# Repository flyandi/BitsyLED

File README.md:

<h1 align="center">
	
	<br />
	BitsyLED 
</h1>
<p align="center">
	A minimal firmware and configurator to drive RGB LED's
</p>

---

Click below for a video:

# Introduction

BitsyLED is a minimal firmware to drive RGB LED's (WS2811, WS2812, NeoPixels, etc). It's designed for anything RC but also can be used for other projects including Christmas lights, Lego's, or even your real car.

BitsyLED is divided into two parts: The Firmware and the Configurator. The firmware can be run on most Arduino compatible boards and I also created a dedicated board (see below) that is targeted primarily for RC purposes.

## Features

By default the firmware is set to the following settings which is the maximum amount supported by the ATTINY. The firmware can be reconfigured through the file `config.h`.

* Up to 5 individual ranges, selectable through either an RC PWM signal, Analog signal, Time based or always on.

* 3 LED data strands per range (Left, Right, Other)

* Each data strand can have up to 10 LED's

* Supports multiple patterns such as Off, Solid, Blink, Strobe and Pulse. 

* Supports different speeds per pattern

* Simulate your patterns directly through the BitsyLED configurator

## Status

The configurator and firmware are still under development but some parts may change as I have time to complete the following objectives:

- Introduce curves for custom light patterns (Pending)
- Add presets (Pending)
- Add serial debug output (In Progress)
- More documentation (getting there)
- Upload firmware directly from the configurator (Pending)

## Firmware

The firmware is designed for Arduino compatible boards. I also created a dedicated board called the BitsyLED board.

The default firmware configuration is setup for the BitsyLED board which sports a 8bit ATTINY84 that supports up to 5 selectable configurations. Each configuration can have 3 data strands with up to 10 LED's per strand. 

The firmware can be reconfigured as needed via the `config.h` file. 

### Board Support

| Board | Ranges | Strands/Range | LED's/Strand | Possible Combinations | Config |
| ----  | ------ | ------------- | ------------ | --------------------- | ------- | 
| BitsyLED | 5 | 3 | 10 | 150 | `BOARD_BITSYLED` in `config.h` |
| Arduino | 6 | 3 | 25 | 450 | `BOARD_ARDUINO` in `config.h` |

## Configurator

The configurator is a visual tool that allows easy setup of LED's and supports various effects such blinking, strobe and pulsing.

It allows to setup different selectable ranges which can be controlled via an PWM RC signal, a 10k Analog Potentiometer or based on Time (TBD).

### Installation

The configurator is available as standalone app since Google has dropped support for Chrome Apps. Please download the latest release for your platform from the `releases` tab.

Once installed, the application will automatically updates itself once new versions are released.

## Hardware

Right now I don't offer a complete build of the BitsyLED board however you can order your own copy on Oshpark. 

Alternatively the firmware runs perfectly fine on any Arduino compatible board with the caveat that the firmware and configurator settings are statically aligned to the Arduino Pro Mini with a maximum of 1024bytes of EEPROM.

### v1.2.1 (Latest)

https://oshpark.com/shared_projects/B3IAiNyH

I created a new board that is slimmer and has SMD pad's instead of the drill pad's which gives it more flexibility. The board also comes with an status LED.

#### Parts

All parts available on DigiKey.com. I changed some components in this version!

- 1x ATTINY84 (Part ATTINY84A-SSURCT-ND) 
- 1x Capacitor in 805 packaging (587-1304-1-ND) 
- 1x Diode in SOD-123 packaging (MMSZ5231B-TP)
- 1x Blue LED in 805 packaging (150080BS75000)
- 1x Resistor in 805 packaging with value of 140ohms (Part RMCF0805FT140R)

#### How to use the board

The board is divided into a top and bottom part. The top part includes the three data channel (Left, Right, Other) as well the input (RC, Analog). The header is designed to be foremost compatible with RC PWM signals (Signal + 5V + GND). 

Be careful not to mix up the upper and lower header from the front side as they are aligned with each other.

The board has 3 LED channels: Left, Right and Other; plus an input channel that either can be served by an RC-PWM or Analog signal. Ensure that your configuration includes the proper input.

The bottom board includes the same 6 position header however it's being used for two purposes: Firmware updates and Configuration.

Follow the connection diagram above how to connect your LED's and Input's.

You will need an USBASP to upload the Firmware and an serial capable board (like FTDI adapter) to upload the configuration from the configurator.

### v1.1 (For reference only)

https://oshpark.com/shared_projects/E85sUqFS

#### Parts

All parts available on DigiKey.com:

- 1x ATTINY84 (Part ATTINY84A-SSURCT-ND) 
- 1x Capacitor in 805 packaging (587-1304-1-ND) 
- 1x Diode in SOD-123 packaging (MMSZ5242B-TPMSCT-ND)

#### How to use the board

The board has 3 LED channels: Left, Right and Other; plus an input channel that either can be served by an RC-PWM or Analog signal. Ensure that your configuration selectest the proper input.

Additionally the board has a top and bottom SMD connector that is used as a dual function to upload the firmware and as serial port.

Follow the connection diagram below how to connect 

You will need an USBASP to upload the Firmware and an serial capable board (like FTDI adapter) to upload the configuration from the configurator.

### Future

Working on a new board with USB support.

### Arduino

As described above, the Arduino configuraton is statically aligned for the Arduino Pro Mini series which has by default an EEPROM size of `1024 bytes`.

However that amount of storage still results in up to `6` selectable ranges, each with `3` strands and up to `25` led's per strand.

The following pin map is being used for BitsyLED:

| Pin | Purpose | 
| ----  | ------ |
| 9 | Input for RC PWM or Analog |
| 10 | Left Strand Data Channel |
| 11 | Right Strand Data Channel |
| 12 | Other Strand Data Channel |

Also if enabled, BitsyLED will use the internal LED on pin `13` as status LED.

## Installation

Please download the latest binary from the releases tab or clone this project and build your own version. 

For firmware, you will need the Arduino IDE (easiest). Clone this project and ipen the `bitsyled.ino` in the `firmware` folder. Follow the direction for your board to upload.

For the BitsyLED board you need to install ATTINY board support into your IDE.

## Links

For support, help or discussion please visit my official thread on RCGroups: 

https://www.rcgroups.com/forums/showthread.php?3289805-BitsyLED

For regular project updates please visit the project on hackaday.io:

https://hackaday.io/project/165227-bitsyled

## License

This program is free software: you can redistribute it and/or modify
it under the terms of the GNU General Public License as published by
the Free Software Foundation, either version 3 of the License, or
(at your option) any later version.

This program is distributed in the hope that it will be useful,
but WITHOUT ANY WARRANTY; without even the implied warranty of
MERCHANTABILITY or FITNESS FOR A PARTICULAR PURPOSE. See the
GNU General Public License for more details.

You should have received a copy of the GNU General Public License
along with this program. If not, see <http://www.gnu.org/licenses/>

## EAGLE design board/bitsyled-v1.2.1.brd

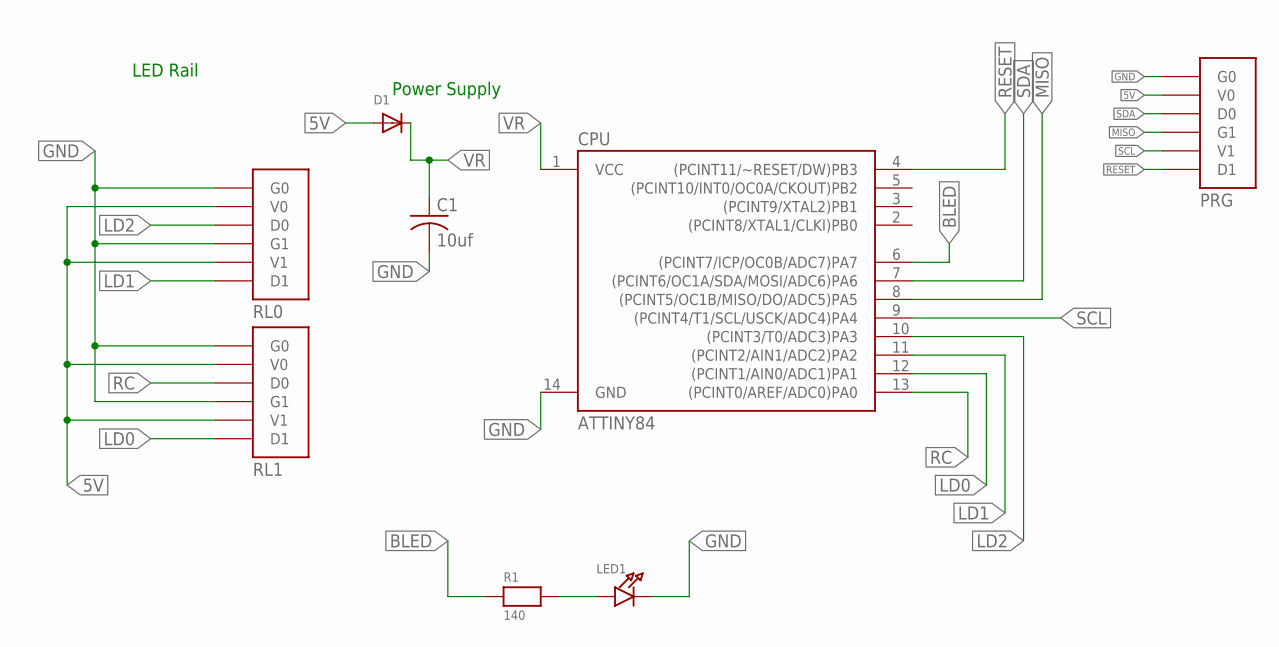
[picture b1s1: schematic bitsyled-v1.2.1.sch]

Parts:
C1: 10uf; C0805
CPU: ATTINY84; SO14
D1: DIODESOD-123; SOD-123
LED1: LED0805_NOOUTLINE; CHIPLED_0805_NOOUTLINE
PRG: BITSYLED_1X6_RAILPRG; BITSYLED_1X6_RAIL_PRG
R1: 140; _0805
RL0: BITSYLED_1X6_RAILNORMAL; BITSYLED_1X6_RAIL
RL1: BITSYLED_1X6_RAILREVERSED; BITSYLED_1X6_RAIL_R

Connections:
5V: D1.A, PRG.V0, RL0.V0, RL0.V1, RL1.V0, RL1.V1
BLED: CPU.6 ((PCINT7/ICP/OC0B/ADC7)PA7), R1.1
GND: C1.2, CPU.14 (GND), LED1.C, PRG.G0, RL0.G0, RL0.G1, RL1.G0, RL1.G1
LD0: CPU.12 ((PCINT1/AIN0/ADC1)PA1), RL1.D1
LD1: CPU.11 ((PCINT2/AIN1/ADC2)PA2), RL0.D1
LD2: CPU.10 ((PCINT3/T0/ADC3)PA3), RL0.D0
MISO: CPU.8 ((PCINT5/OC1B/MISO/DO/ADC5)PA5), PRG.G1
unnamed: LED1.A, R1.2
RC: CPU.13 ((PCINT0/AREF/ADC0)PA0), RL1.D0
RESET: CPU.4 ((PCINT11/~RESET/DW)PB3), PRG.D1
SCL: CPU.9 ((PCINT4/T1/SCL/USCK/ADC4)PA4), PRG.V1
SDA: CPU.7 ((PCINT6/OC1A/SDA/MOSI/ADC6)PA6), PRG.D0
VR: C1.1, CPU.1 (VCC), D1.C

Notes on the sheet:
Power Supply
LED Rail

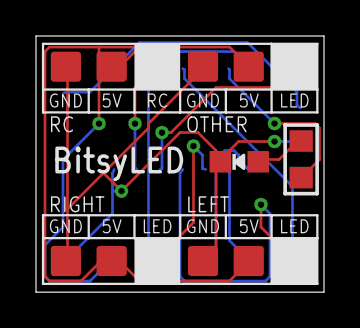
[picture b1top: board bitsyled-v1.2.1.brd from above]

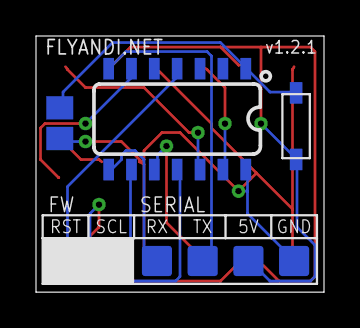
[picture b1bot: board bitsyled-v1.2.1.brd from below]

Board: 2 copper layers, 16.0 x 14.2 mm, 8 parts (3 on the bottom side), 13 nets.

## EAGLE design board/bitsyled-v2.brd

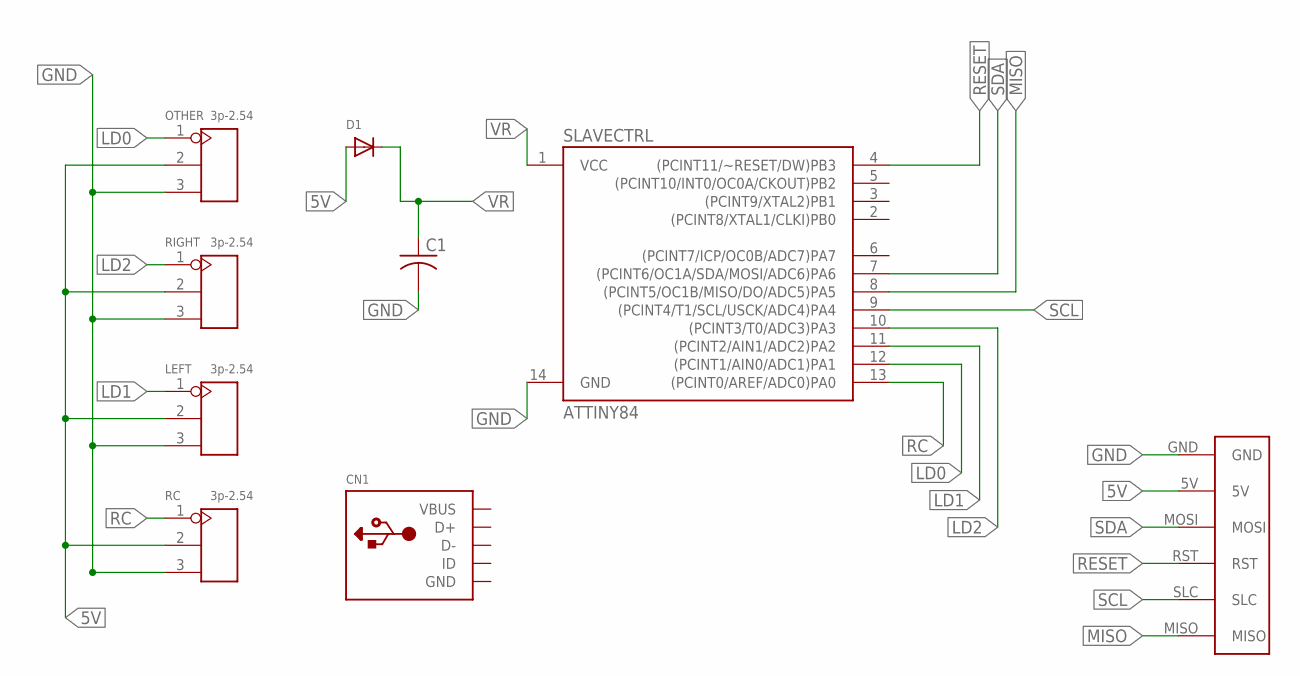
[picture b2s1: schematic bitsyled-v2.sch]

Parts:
C1: C-USC0805; C0805
CN1: USBMOLEX; USB-MINIB-THM-MOLEX
D1: DIODESOD-123; SOD-123
LEFT: 3p-2.54; H3-2.54
OTHER: 3p-2.54; H3-2.54
RC: 3p-2.54; H3-2.54
RIGHT: 3p-2.54; H3-2.54
SLAVECTRL: ATTINY84; SO14
U$1: SMDPAD_PRG

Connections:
5V: D1.A, LEFT.2, OTHER.2, RC.2, RIGHT.2, U$1.5V
GND: C1.2, CN1.GND, LEFT.3, OTHER.3, RC.3, RIGHT.3, SLAVECTRL.14 (GND), U$1.GND
LD0: OTHER.1, SLAVECTRL.12 ((PCINT1/AIN0/ADC1)PA1)
LD1: LEFT.1, SLAVECTRL.11 ((PCINT2/AIN1/ADC2)PA2)
LD2: RIGHT.1, SLAVECTRL.10 ((PCINT3/T0/ADC3)PA3)
MISO: SLAVECTRL.8 ((PCINT5/OC1B/MISO/DO/ADC5)PA5), U$1.MISO
RC: RC.1, SLAVECTRL.13 ((PCINT0/AREF/ADC0)PA0)
RESET: SLAVECTRL.4 ((PCINT11/~RESET/DW)PB3), U$1.RST
SCL: SLAVECTRL.9 ((PCINT4/T1/SCL/USCK/ADC4)PA4), U$1.SLC
SDA: SLAVECTRL.7 ((PCINT6/OC1A/SDA/MOSI/ADC6)PA6), U$1.MOSI
VBUS: CN1.VBUS
VR: C1.1, D1.C, SLAVECTRL.1 (VCC)

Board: 2 copper layers, 9 parts (1 on the bottom side), 11 nets, no tracks yet.

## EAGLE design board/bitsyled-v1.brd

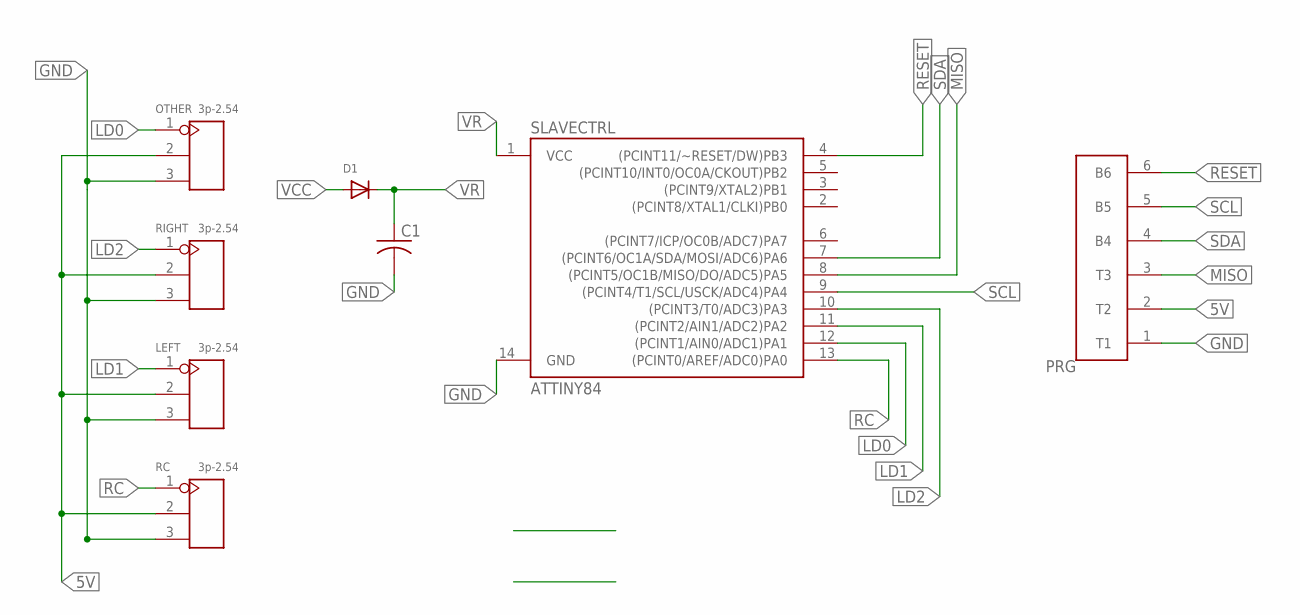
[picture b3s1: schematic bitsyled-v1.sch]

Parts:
C1: C-USC0805; C0805
D1: DIODESOD-123; SOD-123
LEFT: 3p-2.54; H3-2.54
OTHER: 3p-2.54; H3-2.54
PRG: SMDPAD_TB_3X3
RC: 3p-2.54; H3-2.54
RIGHT: 3p-2.54; H3-2.54
SLAVECTRL: ATTINY84; SO14

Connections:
5V: LEFT.2, OTHER.2, PRG.2 (T2), RC.2, RIGHT.2
GND: C1.2, LEFT.3, OTHER.3, PRG.1 (T1), RC.3, RIGHT.3, SLAVECTRL.14 (GND)
LD0: OTHER.1, SLAVECTRL.12 ((PCINT1/AIN0/ADC1)PA1)
LD1: LEFT.1, SLAVECTRL.11 ((PCINT2/AIN1/ADC2)PA2)
LD2: RIGHT.1, SLAVECTRL.10 ((PCINT3/T0/ADC3)PA3)
MISO: PRG.3 (T3), SLAVECTRL.8 ((PCINT5/OC1B/MISO/DO/ADC5)PA5)
RC: RC.1, SLAVECTRL.13 ((PCINT0/AREF/ADC0)PA0)
RESET: PRG.6 (B6), SLAVECTRL.4 ((PCINT11/~RESET/DW)PB3)
SCL: PRG.5 (B5), SLAVECTRL.9 ((PCINT4/T1/SCL/USCK/ADC4)PA4)
SDA: PRG.4 (B4), SLAVECTRL.7 ((PCINT6/OC1A/SDA/MOSI/ADC6)PA6)
VCC: D1.A
VR: C1.1, SLAVECTRL.1 (VCC)

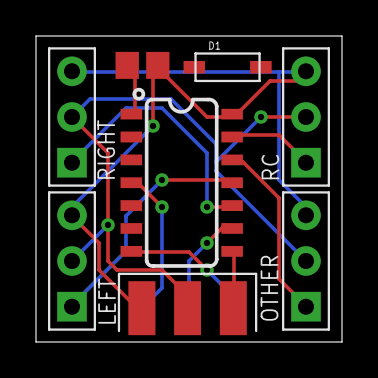
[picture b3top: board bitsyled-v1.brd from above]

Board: 2 copper layers, 17.0 x 17.0 mm, 8 parts (0 on the bottom side), 11 nets.

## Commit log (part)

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2019-04-15 initial
2019-04-15 cleanup
2019-04-15 Logo updates
2019-04-22 Updatez
2019-04-22 Updates docs
2019-04-23 adds build process
2019-04-23 travis build test
2019-04-23 updates travis
2019-04-26 Adds time based support and Arduino firmware
2019-04-26 Enable BitsyLED by default
2019-04-26 Updates readme
2019-04-27 update docs
2019-04-28 upd doc
2019-05-02 Some presets
2019-05-12 Firmware 1.03 update
2019-05-12 1.2.1 board updates
2019-09-12 Bump mixin-deep from 1.3.1 to 1.3.2 in /configurator
    Bumps [mixin-deep](https://github.com/jonschlinkert/mixin-deep) from 1.3.1 to 1.3.2.
    - [Release notes](https://github.com/jonschlinkert/mixin-deep/releases)
    - [Commits](https://github.com/jonschlinkert/mixin-deep/compare/1.3.1...1.3.2)
2019-09-15 Improves serial communication and eeprom safety
2020-03-14 Bump acorn from 5.7.3 to 5.7.4 in /configurator
    Bumps [acorn](https://github.com/acornjs/acorn) from 5.7.3 to 5.7.4.
    - [Release notes](https://github.com/acornjs/acorn/releases)
    - [Commits](https://github.com/acornjs/acorn/compare/5.7.3...5.7.4)
2020-06-06 Bump websocket-extensions from 0.1.3 to 0.1.4 in /configurator
    Bumps [websocket-extensions](https://github.com/faye/websocket-extensions-node) from 0.1.3 to 0.1.4.
    - [Release notes](https://github.com/faye/websocket-extensions-node/releases)
    - [Changelog](https://github.com/faye/websocket-extensions-node/blob/master/CHANGELOG.md)
    - [Commits](https://github.com/faye/websocket-extensions-node/compare/0.1.3...0.1.4)
2020-07-07 Bump electron from 4.2.10 to 7.2.4 in /configurator
    Bumps [electron](https://github.com/electron/electron) from 4.2.10 to 7.2.4.
    - [Release notes](https://github.com/electron/electron/releases)
    - [Changelog](https://github.com/electron/electron/blob/master/docs/breaking-changes.md)
    - [Commits](https://github.com/electron/electron/compare/v4.2.10...v7.2.4)
2020-09-03 Bump bl from 3.0.0 to 3.0.1 in /configurator
    Bumps [bl](https://github.com/rvagg/bl) from 3.0.0 to 3.0.1.
    - [Release notes](https://github.com/rvagg/bl/releases)
    - [Commits](https://github.com/rvagg/bl/compare/v3.0.0...v3.0.1)
2020-09-08 Bump http-proxy from 1.17.0 to 1.18.1 in /configurator
    Bumps [http-proxy](https://github.com/http-party/node-http-proxy) from 1.17.0 to 1.18.1.
    - [Release notes](https://github.com/http-party/node-http-proxy/releases)
    - [Changelog](https://github.com/http-party/node-http-proxy/blob/master/CHANGELOG.md)
    - [Commits](https://github.com/http-party/node-http-proxy/compare/1.17.0...1.18.1)
2021-01-28 Bump electron from 4.2.10 to 9.4.0 in /configurator
    Bumps [electron](https://github.com/electron/electron) from 4.2.10 to 9.4.0.
    - [Release notes](https://github.com/electron/electron/releases)
    - [Changelog](https://github.com/electron/electron/blob/master/docs/breaking-changes.md)
    - [Commits](https://github.com/electron/electron/compare/v4.2.10...v9.4.0)
2021-03-09 Bump elliptic from 6.5.1 to 6.5.4 in /configurator
    Bumps [elliptic](https://github.com/indutny/elliptic) from 6.5.1 to 6.5.4.
    - [Release notes](https://github.com/indutny/elliptic/releases)
    - [Commits](https://github.com/indutny/elliptic/compare/v6.5.1...v6.5.4)
2021-03-30 Bump y18n from 3.2.1 to 3.2.2 in /configurator
    Bumps [y18n](https://github.com/yargs/y18n) from 3.2.1 to 3.2.2.
    - [Release notes](https://github.com/yargs/y18n/releases)
    - [Changelog](https://github.com/yargs/y18n/blob/master/CHANGELOG.md)
    - [Commits](https://github.com/yargs/y18n/commits)
2021-05-06 Bump ua-parser-js from 0.7.20 to 0.7.28 in /configurator
    Bumps [ua-parser-js](https://github.com/faisalman/ua-parser-js) from 0.7.20 to 0.7.28.
    - [Release notes](https://github.com/faisalman/ua-parser-js/releases)
    - [Commits](https://github.com/faisalman/ua-parser-js/compare/0.7.20...0.7.28)
2021-05-07 Bump handlebars from 4.5.3 to 4.7.7 in /configurator
    Bumps [handlebars](https://github.com/wycats/handlebars.js) from 4.5.3 to 4.7.7.
    - [Release notes](https://github.com/wycats/handlebars.js/releases)
    - [Changelog](https://github.com/handlebars-lang/handlebars.js/blob/master/release-notes.md)
    - [Commits](https://github.com/wycats/handlebars.js/compare/v4.5.3...v4.7.7)
2021-05-10 Bump hosted-git-info from 2.8.4 to 2.8.9 in /configurator
    Bumps [hosted-git-info](https://github.com/npm/hosted-git-info) from 2.8.4 to 2.8.9.
    - [Release notes](https://github.com/npm/hosted-git-info/releases)
    - [Changelog](https://github.com/npm/hosted-git-info/blob/v2.8.9/CHANGELOG.md)
    - [Commits](https://github.com/npm/hosted-git-info/compare/v2.8.4...v2.8.9)
2021-05-27 Bump dns-packet from 1.3.1 to 1.3.4 in /configurator
    Bumps [dns-packet](https://github.com/mafintosh/dns-packet) from 1.3.1 to 1.3.4.
    - [Release notes](https://github.com/mafintosh/dns-packet/releases)
    - [Changelog](https://github.com/mafintosh/dns-packet/blob/master/CHANGELOG.md)
    - [Commits](https://github.com/mafintosh/dns-packet/compare/v1.3.1...v1.3.4)
2021-06-07 Bump merge-deep from 3.0.2 to 3.0.3 in /configurator
    Bumps [merge-deep](https://github.com/jonschlinkert/merge-deep) from 3.0.2 to 3.0.3.
    - [Release notes](https://github.com/jonschlinkert/merge-deep/releases)
    - [Commits](https://github.com/jonschlinkert/merge-deep/compare/3.0.2...3.0.3)
    ---
    updated-dependencies:
    - dependency-name: merge-deep
2021-08-10 Bump path-parse from 1.0.6 to 1.0.7 in /configurator
    Bumps [path-parse](https://github.com/jbgutierrez/path-parse) from 1.0.6 to 1.0.7.
    - [Release notes](https://github.com/jbgutierrez/path-parse/releases)
    - [Commits](https://github.com/jbgutierrez/path-parse/commits/v1.0.7)
    ---
    updated-dependencies:
    - dependency-name: path-parse
2021-09-21 Bump tmpl from 1.0.4 to 1.0.5 in /configurator
    Bumps [tmpl](https://github.com/daaku/nodejs-tmpl) from 1.0.4 to 1.0.5.
    - [Release notes](https://github.com/daaku/nodejs-tmpl/releases)
    - [Commits](https://github.com/daaku/nodejs-tmpl/commits/v1.0.5)
    ---
    updated-dependencies:
    - dependency-name: tmpl
2022-01-13 Bump follow-redirects from 1.9.0 to 1.14.7 in /configurator
    Bumps [follow-redirects](https://github.com/follow-redirects/follow-redirects) from 1.9.0 to 1.14.7.
    - [Release notes](https://github.com/follow-redirects/follow-redirects/releases)
    - [Commits](https://github.com/follow-redirects/follow-redirects/compare/v1.9.0...v1.14.7)
    ---
    updated-dependencies:
    - dependency-name: follow-redirects
2022-02-12 Bump follow-redirects from 1.9.0 to 1.14.8 in /configurator
    Bumps [follow-redirects](https://github.com/follow-redirects/follow-redirects) from 1.9.0 to 1.14.8.
    - [Release notes](https://github.com/follow-redirects/follow-redirects/releases)
    - [Commits](https://github.com/follow-redirects/follow-redirects/compare/v1.9.0...v1.14.8)
    ---
    updated-dependencies:
    - dependency-name: follow-redirects
2022-02-17 Bump url-parse from 1.4.7 to 1.5.7 in /configurator
    Bumps [url-parse](https://github.com/unshiftio/url-parse) from 1.4.7 to 1.5.7.
    - [Release notes](https://github.com/unshiftio/url-parse/releases)
    - [Commits](https://github.com/unshiftio/url-parse/compare/1.4.7...1.5.7)
    ---
    updated-dependencies:
    - dependency-name: url-parse
2022-03-01 Bump plist from 3.0.1 to 3.0.4 in /configurator
    Bumps [plist](https://github.com/TooTallNate/node-plist) from 3.0.1 to 3.0.4.
    - [Release notes](https://github.com/TooTallNate/node-plist/releases)
    - [Changelog](https://github.com/TooTallNate/plist.js/blob/master/History.md)
    - [Commits](https://github.com/TooTallNate/node-plist/commits)
    ---
    updated-dependencies:
2022-03-02 Bump color-string from 1.5.3 to 1.9.0 in /configurator
    Bumps [color-string](https://github.com/Qix-/color-string) from 1.5.3 to 1.9.0.
    - [Release notes](https://github.com/Qix-/color-string/releases)
    - [Changelog](https://github.com/Qix-/color-string/blob/master/CHANGELOG.md)
    - [Commits](https://github.com/Qix-/color-string/commits/1.9.0)
    ---
    updated-dependencies:
2022-03-02 Bump ws from 5.2.2 to 5.2.3 in /configurator
    Bumps [ws](https://github.com/websockets/ws) from 5.2.2 to 5.2.3.
    - [Release notes](https://github.com/websockets/ws/releases)
    - [Commits](https://github.com/websockets/ws/compare/5.2.2...5.2.3)
    ---
    updated-dependencies:
    - dependency-name: ws
2022-03-02 Bump electron from 4.2.10 to 11.5.0 in /configurator
    Bumps [electron](https://github.com/electron/electron) from 4.2.10 to 11.5.0.
    - [Release notes](https://github.com/electron/electron/releases)
    - [Changelog](https://github.com/electron/electron/blob/main/docs/breaking-changes.md)
    - [Commits](https://github.com/electron/electron/compare/v4.2.10...v11.5.0)
    ---
    updated-dependencies:
2022-03-02 Bump tar from 4.4.10 to 4.4.19 in /configurator
    Bumps [tar](https://github.com/npm/node-tar) from 4.4.10 to 4.4.19.
    - [Release notes](https://github.com/npm/node-tar/releases)
    - [Changelog](https://github.com/npm/node-tar/blob/main/CHANGELOG.md)
    - [Commits](https://github.com/npm/node-tar/compare/v4.4.10...v4.4.19)
    ---
    updated-dependencies:
2022-03-25 Bump electron from 4.2.10 to 13.6.6 in /configurator
    Bumps [electron](https://github.com/electron/electron) from 4.2.10 to 13.6.6.
    - [Release notes](https://github.com/electron/electron/releases)
    - [Changelog](https://github.com/electron/electron/blob/main/docs/breaking-changes.md)
    - [Commits](https://github.com/electron/electron/compare/v4.2.10...v13.6.6)
    ---
    updated-dependencies:
2022-06-01 Bump eventsource from 1.0.7 to 1.1.1 in /configurator
    Bumps [eventsource](https://github.com/EventSource/eventsource) from 1.0.7 to 1.1.1.
    - [Release notes](https://github.com/EventSource/eventsource/releases)
    - [Changelog](https://github.com/EventSource/eventsource/blob/master/HISTORY.md)
    - [Commits](https://github.com/EventSource/eventsource/compare/v1.0.7...v1.1.1)
    ---
    updated-dependencies:
2022-11-10 Bump electron from 4.2.10 to 18.3.7 in /configurator
    Bumps [electron](https://github.com/electron/electron) from 4.2.10 to 18.3.7.
    - [Release notes](https://github.com/electron/electron/releases)
    - [Changelog](https://github.com/electron/electron/blob/main/docs/breaking-changes.md)
    - [Commits](https://github.com/electron/electron/compare/v4.2.10...v18.3.7)
    ---
    updated-dependencies:
2022-12-03 Bump decode-uri-component from 0.2.0 to 0.2.2 in /configurator
    Bumps [decode-uri-component](https://github.com/SamVerschueren/decode-uri-component) from 0.2.0 to 0.2.2.
    - [Release notes](https://github.com/SamVerschueren/decode-uri-component/releases)
    - [Commits](https://github.com/SamVerschueren/decode-uri-component/compare/v0.2.0...v0.2.2)
    ---
    updated-dependencies:
    - dependency-name: decode-uri-component
2022-12-08 Bump qs from 6.5.2 to 6.5.3 in /configurator
    Bumps [qs](https://github.com/ljharb/qs) from 6.5.2 to 6.5.3.
    - [Release notes](https://github.com/ljharb/qs/releases)
    - [Changelog](https://github.com/ljharb/qs/blob/main/CHANGELOG.md)
    - [Commits](https://github.com/ljharb/qs/compare/v6.5.2...v6.5.3)
    ---
    updated-dependencies:
2023-01-26 Bump ua-parser-js from 0.7.20 to 0.7.33 in /configurator
    Bumps [ua-parser-js](https://github.com/faisalman/ua-parser-js) from 0.7.20 to 0.7.33.
    - [Release notes](https://github.com/faisalman/ua-parser-js/releases)
    - [Changelog](https://github.com/faisalman/ua-parser-js/blob/master/changelog.md)
    - [Commits](https://github.com/faisalman/ua-parser-js/compare/0.7.20...0.7.33)
    ---
    updated-dependencies:

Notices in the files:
parts and their libraries:
SparkFun-IC-Microcontroller: Licensing: Creative Commons ShareAlike 4.0 International - https://creativecommons.org/licenses/by-sa/4.0
microbuilder: This work is placed in the public domain, and may be freely used for commercial and non-commercial work with the following conditions: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
